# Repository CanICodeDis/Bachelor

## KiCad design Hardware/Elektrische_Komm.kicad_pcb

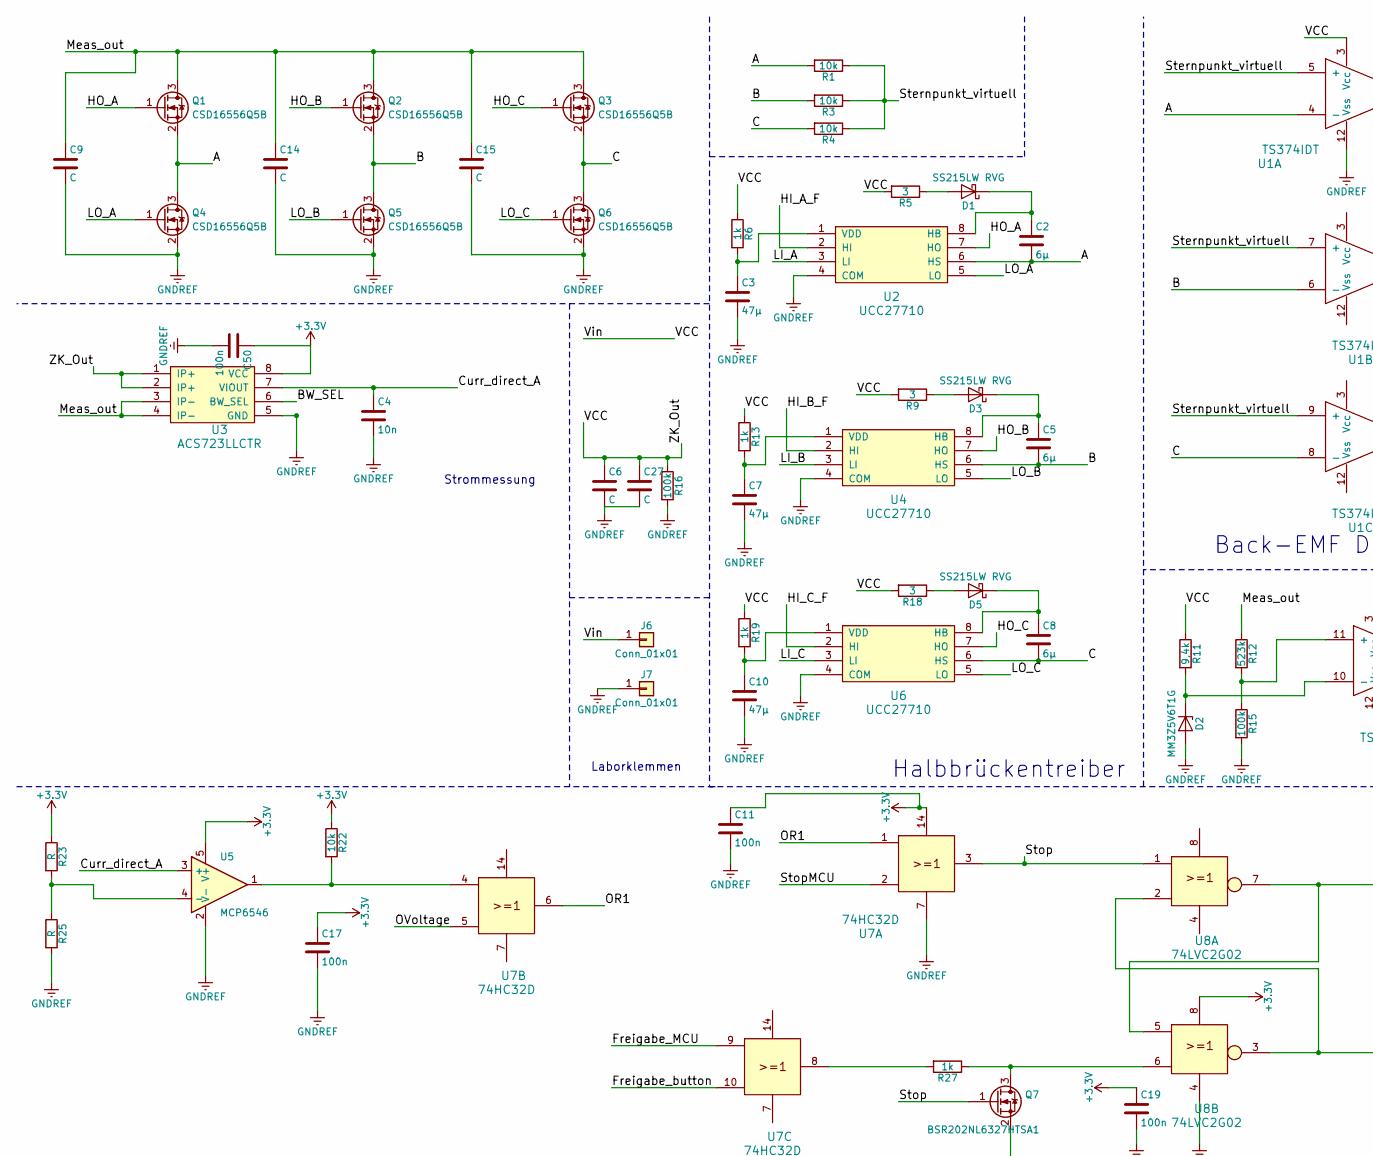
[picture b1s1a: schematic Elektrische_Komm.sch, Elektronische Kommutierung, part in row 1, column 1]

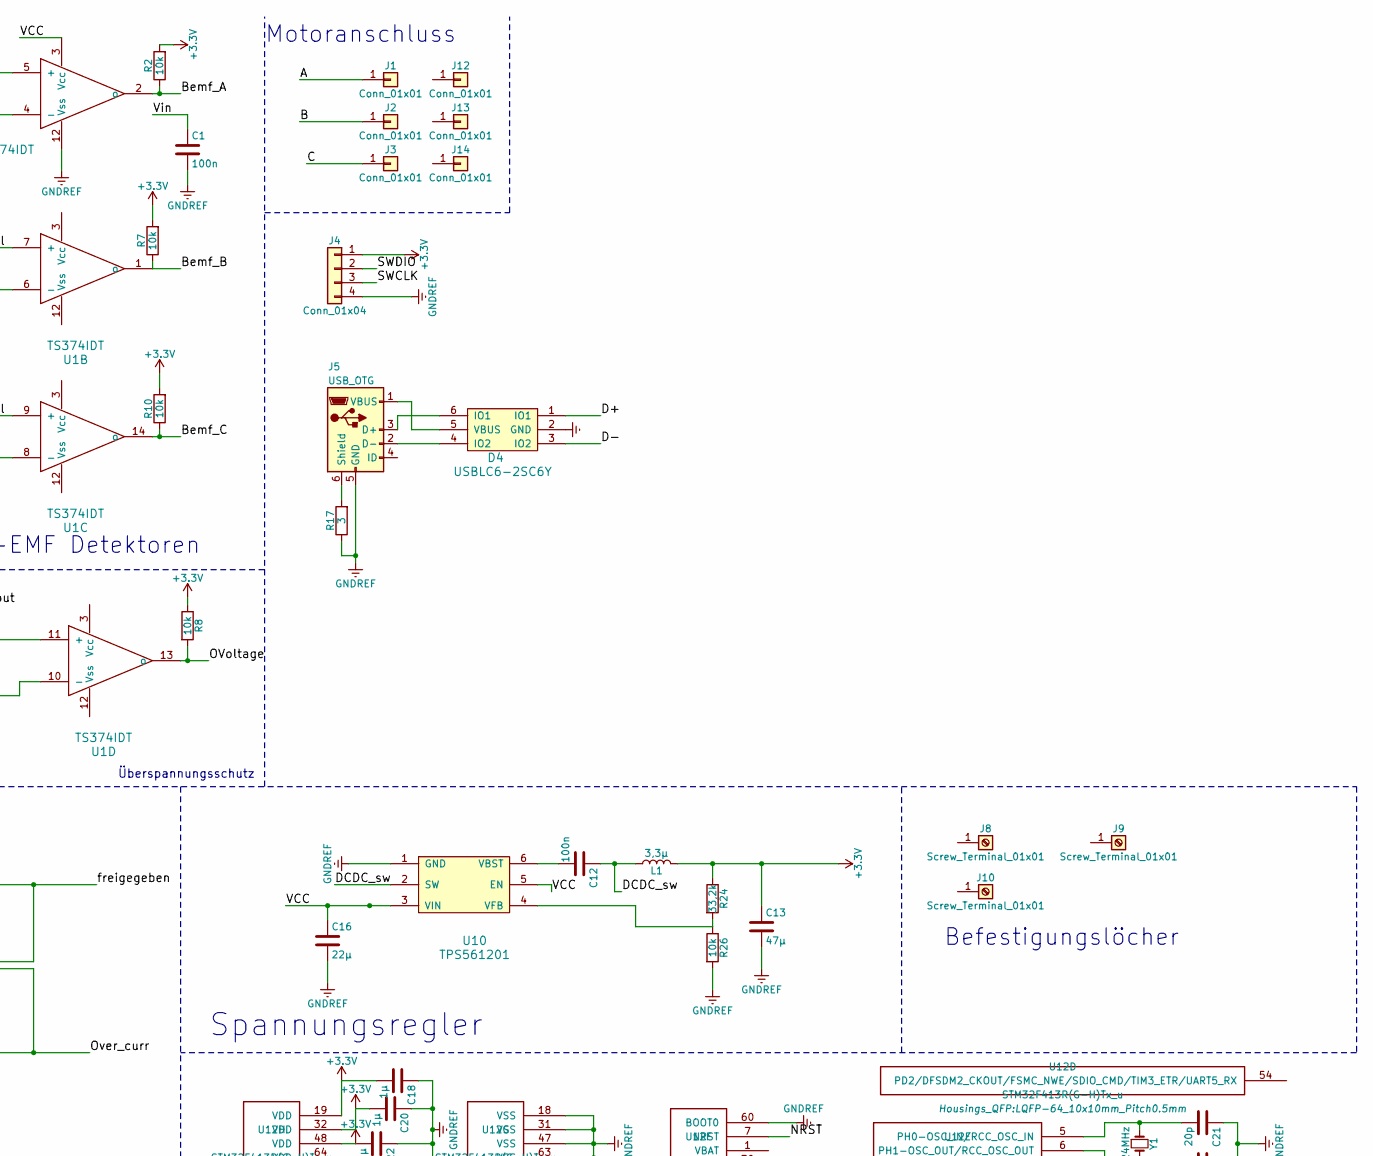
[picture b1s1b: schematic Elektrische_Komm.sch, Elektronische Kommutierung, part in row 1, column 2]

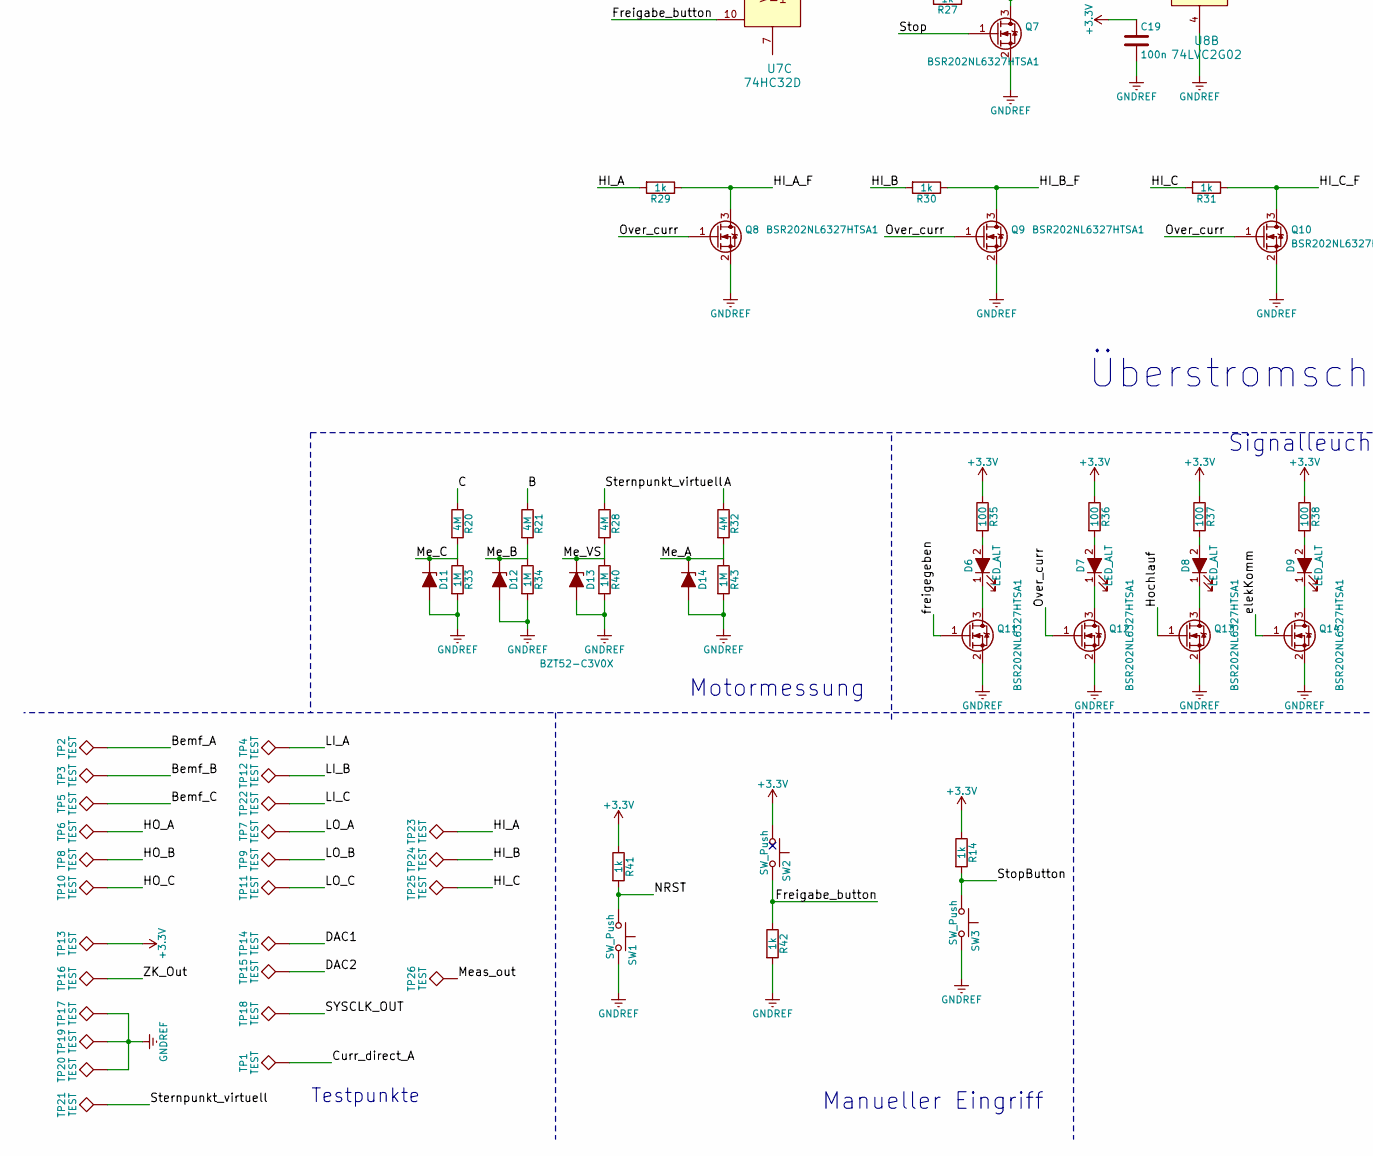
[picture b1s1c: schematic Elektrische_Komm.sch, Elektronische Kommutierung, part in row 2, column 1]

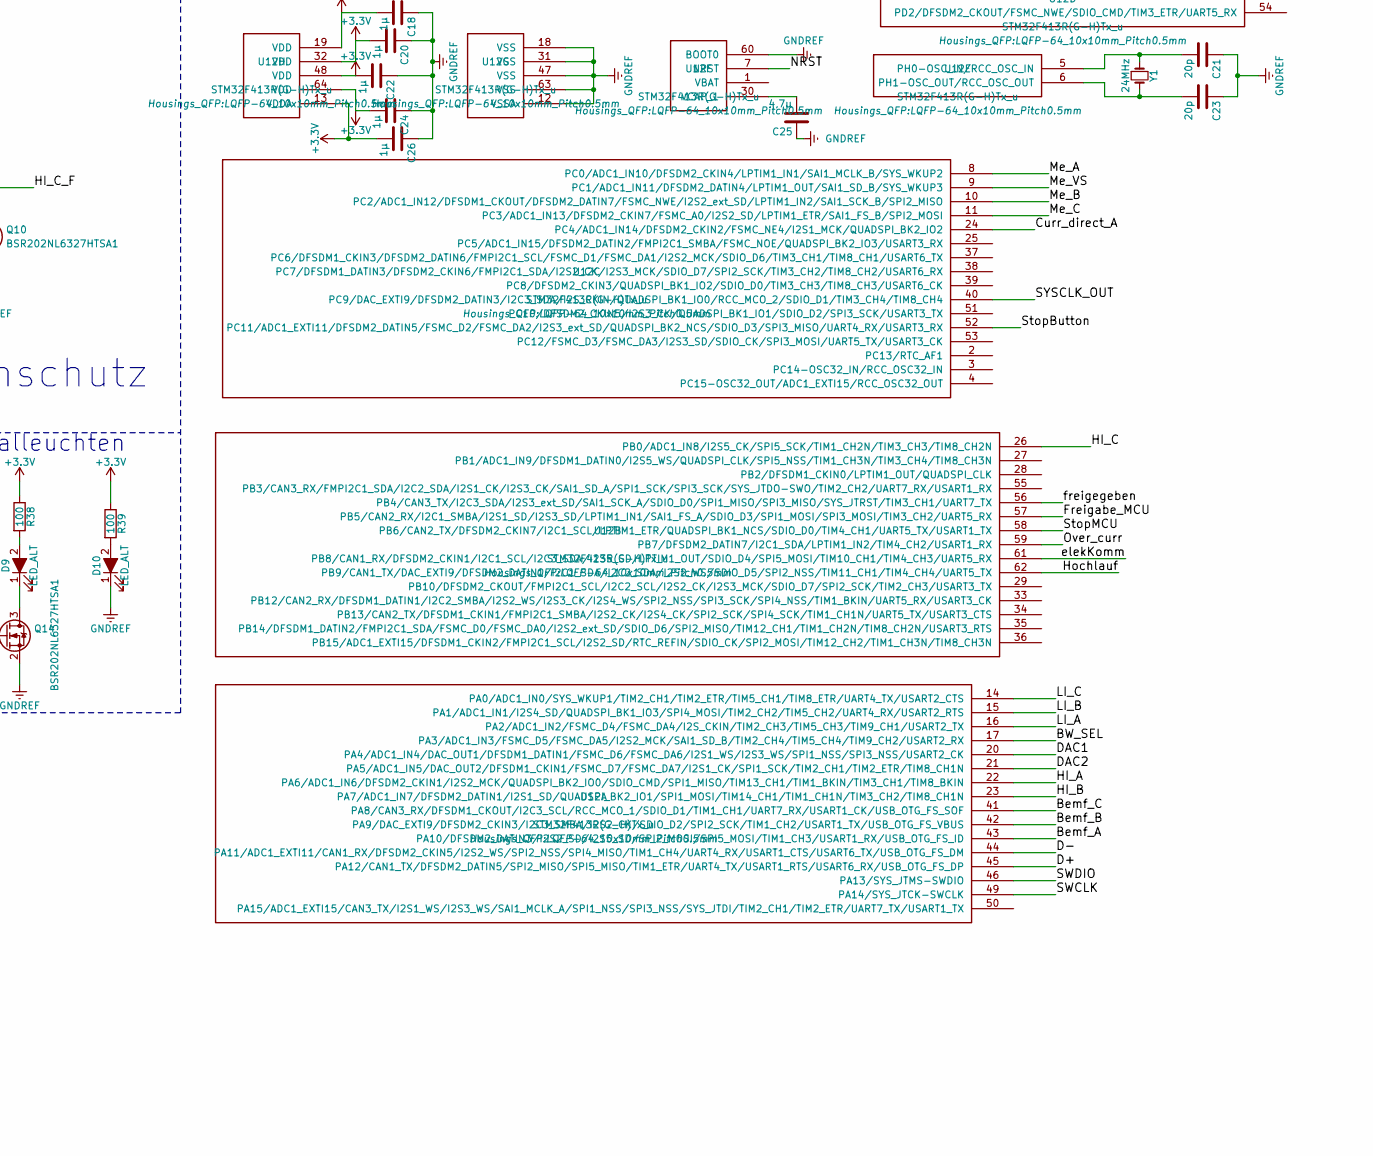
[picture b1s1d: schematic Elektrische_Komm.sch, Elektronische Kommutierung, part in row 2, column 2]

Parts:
C1, C11, C12, C17, C19, C50: 100n; C_0603
C2, C5, C8: 6µ; R_0603
C3, C7, C10, C13: 47µ; C_0805
C4: 10n; C_0603
C6, C27: C; CP_Radial_D10.0mm_P5.00mm
C9, C14, C15: C; C_1812
C16: 22µ; C_1210
C18, C20, C22, C24, C26: 1µ; C_0603
C21, C23: 20p; C_0603
C25: 4,7µ; C_0603
D1, D3, D5: SS215LW RVG; D_SOD-123F
D2: MM3Z5V6T1G; D_SOD-323
D4: USBLC6-2SC6Y; SOT-23-6
D6, D7: LED_ALT; LED_0805_HandSoldering
D8, D9, D10: LED_ALT; LED_0805
D11, D12, D13, D14: BZT52-C3V0X; D_SOD-123
J1, J2, J3: Conn_01x01; MotorConn
J4: Conn_01x04; JST_EH_B04B-EH-A_04x2.50mm_Straight
J5: USB_OTG; USB_Micro-B_Molex-105017-0001
J6, J7: Conn_01x01; Laborbuchse
J8, J9, J10: Screw_Terminal_01x01; MountingHole_3.2mm_M3_DIN965
J12, J13, J14: Conn_01x01; Führungsloch
L1: 3,3µ; SRN3015-3R3M
Q1, Q2, Q3, Q4, Q5, Q6: CSD16556Q5B; SON5x6
Q7, Q8, Q9, Q10, Q11, Q12, Q13, Q14: BSR202NL6327HTSA1; SC-59
R1, R2, R3, R4, R7, R8, R10, R22, R26: 10k; R_0603
R5, R9, R18: 3; R_1210
R6, R13, R14, R19, R27, R29, R30, R31, R41, R42: 1k; R_0603
R11: 9,4k; R_0603
R12: 523k; R_0603
R15, R16: 100k; R_0603
R17: 3; R_0603
R20, R21, R28, R32: 4M; R_0603
R23, R25: R; R_0603
R24: 33,2k; R_0603
R33, R34, R40, R43: 1M; R_0603
R35, R36, R37, R38, R39: 100; R_0603
SW1, SW2, SW3: SW_Push; Switch
TP1, TP2, TP3, TP4, TP5, TP6, TP7, TP8, TP9, TP10, TP11, TP12, TP13, TP14, TP15, TP16, TP17, TP18, TP19, TP20, TP21, TP22, TP23, TP24, TP25, TP26: TEST; Pin_Header_Straight_1x01_Pitch1.00mm
U1: TS374IDT; SOIC-14_3.9x8.7mm_Pitch1.27mm
U2, U4, U6: UCC27710; SOIC-8_3.9x4.9mm_Pitch1.27mm
U3: ACS723LLCTR; SOIC-8_3.9x4.9mm_Pitch1.27mm
U5: MCP6546; SOT-23-5
U7: 74HC32D; TSSOP-14_4.4x5mm_Pitch0.65mm
U8: 74LVC2G02; TSSOP-8_3x3mm_Pitch0.65mm
U10: TPS561201; SOT-23-6
U12: STM32F413R(G-H)Tx_u; LQFP-64_10x10mm_Pitch0.5mm
Y1: 24MHz; FQ5032A

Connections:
+3V3: C11.1, C13.1, C17.1, C18.2, C19.1, C20.2, C22.2, C24.2, C26.2, C50.1, J4.1, L1.2, R2.2, R7.2, R8.1, R10.2, R14.1, R22.1, R23.1, R24.1, R35.1, R36.1, R37.1, R38.1, R39.1, R41.1, SW2.1, TP13.1, U3.8 (VCC), U5.5 (V+), U7.14, U8.8, U12.13 (VDDA), U12.19 (VDD), U12.32 (VDD), U12.48 (VDD), U12.64 (VDD)
/A: C2.2, J1.1, Q1.2 (S), Q4.3 (D), R1.2, R32.1, U1.4 (-), U2.6 (HS)
/B: C5.2, J2.1, Q2.2 (S), Q5.3 (D), R3.2, R21.1, U1.6 (-), U4.6 (HS)
/BW_SEL: U3.6 (BW_SEL), U12.17 (PA3/ADC1_IN3/FSMC_D5/FSMC_DA5/I2S2_MCK/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)
/Bemf_A: R2.1, TP2.1, U1.2 (o), U12.43 (PA10/DFSDM2_DATIN3/I2S2_SD/I2S5_SD/SPI2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)
/Bemf_B: R7.1, TP3.1, U1.1 (o), U12.42 (PA9/DAC_EXTI9/DFSDM2_CKIN3/I2C3_SMBA/I2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)
/Bemf_C: R10.1, TP5.1, U1.14 (o), U12.41 (PA8/CAN3_RX/DFSDM1_CKOUT/I2C3_SCL/RCC_M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)
/C: C8.2, J3.1, Q3.2 (S), Q6.3 (D), R4.2, R20.1, U1.8 (-), U6.6 (HS)
/Curr_direct_A: C4.1, TP1.1, U3.7 (VIOUT), U5.3 (+), U12.24 (PC4/ADC1_IN14/DFSDM2_CKIN2/FSMC_NE4/I2S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)
/D+: D4.1 (IO1), U12.45 (PA12/CAN1_TX/DFSDM2_DATIN5/SPI2_MISO/SP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)
/D-: D4.3 (IO2), U12.44 (PA11/ADC1_EXTI11/CAN1_RX/DFSDM2_CKIN5/I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)
/DAC1: TP14.1, U12.20 (PA4/ADC1_IN4/DAC_OUT1/DFSDM1_DATIN1/FSM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)
/DAC2: TP15.1, U12.21 (PA5/ADC1_IN5/DAC_OUT2/DFSDM1_CKIN1/FSMC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)
/DCDC_sw: C12.1, L1.1, U10.2 (SW)
/Freigabe_MCU: U7.9, U12.57 (PB5/CAN2_RX/I2C1_SMBA/I2S1_SD/I2S3_SD/L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)
/Freigabe_button: R42.1, SW2.2, U7.10
/HI_A: R29.2, TP23.1, U12.22 (PA6/ADC1_IN6/DFSDM2_CKIN1/I2S2_MCK/QUAD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)
/HI_A_F: Q8.3 (D), R29.1, U2.2 (HI)
/HI_B: R30.2, TP24.1, U12.23 (PA7/ADC1_IN7/DFSDM2_DATIN1/I2S1_SD/QUAD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)
/HI_B_F: Q9.3 (D), R30.1, U4.2 (HI)
/HI_C: R31.2, TP25.1, U12.26 (PB0/ADC1_IN8/I2S5_CK/SPI5_SCK/TIM1_CH2N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)
/HI_C_F: Q10.3 (D), R31.1, U6.2 (HI)
/HO_A: Q1.1 (G), TP6.1, U2.7 (HO)
/HO_B: Q2.1 (G), TP8.1, U4.7 (HO)
/HO_C: Q3.1 (G), TP10.1, U6.7 (HO)
/Hochlauf: Q13.1 (G), U12.62 (PB9/CAN1_TX/DAC_EXTI9/DFSDM2_DATIN1/I2C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)
/LI_A: TP4.1, U2.3 (LI), U12.16 (PA2/ADC1_IN2/FSMC_D4/FSMC_DA4/I2S_CKIN/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)
/LI_B: TP12.1, U4.3 (LI), U12.15 (PA1/ADC1_IN1/I2S4_SD/QUADSPI_BK1_IO3/SP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)
/LI_C: TP22.1, U6.3 (LI), U12.14 (PA0/ADC1_IN0/SYS_WKUP1/TIM2_CH1/TIM2_ET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)
/LO_A: Q4.1 (G), TP7.1, U2.5 (LO)
/LO_B: Q5.1 (G), TP9.1, U4.5 (LO)
/LO_C: Q6.1 (G), TP11.1, U6.5 (LO)
/Me_A: D14.1 (K), R32.2, R43.1, U12.8 (PC0/ADC1_IN10/DFSDM2_CKIN4/LPTIM1_IN1/S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)
/Me_B: D12.1 (K), R21.2, R34.1, U12.10 (PC2/ADC1_IN12/DFSDM1_CKOUT/DFSDM2_DATIN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)
/Me_C: D11.1 (K), R20.2, R33.1, U12.11 (PC3/ADC1_IN13/DFSDM2_CKIN7/FSMC_A0/I2S2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)
/Me_VS: D13.1 (K), R28.2, R40.1, U12.9 (PC1/ADC1_IN11/DFSDM2_DATIN4/LPTIM1_OUT/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)
/Meas_out: C9.1, C14.1, C15.1, Q1.3 (D), Q2.3 (D), Q3.3 (D), R12.1, TP26.1, U3.3 (IP-), U3.4 (IP-)
/NRST: R41.2, SW1.1, U12.7 (NRST)
/OR1: U7.1, U7.6
/OVoltage: R8.2, U1.13 (o), U7.5
/Over_curr: Q8.1 (G), Q9.1 (G), Q10.1 (G), Q12.1 (G), U8.2, U8.3, U12.59 (PB7/DFSDM2_DATIN7/I2C1_SDA/LPTIM1_IN2/T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)
/SWCLK: J4.3, U12.49 (PA14/SYS_JTCK-SWCLK)
/SWDIO: J4.2, U12.46 (PA13/SYS_JTMS-SWDIO)
/SYSCLK_OUT: TP18.1, U12.40 (PC9/DAC_EXTI9/DFSDM2_DATIN3/I2C3_SDA/I2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)
/Sternpunkt_virtuell: R1.1, R3.1, R4.1, R28.1, TP21.1, U1.5 (+), U1.7 (+), U1.9 (+)
/Stop: Q7.1 (G), U7.3, U8.1
/StopButton: R14.2, SW3.1, U12.52 (PC11/ADC1_EXTI11/DFSDM2_DATIN5/FSMC_D2/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)
/StopMCU: U7.2, U12.58 (PB6/CAN2_TX/DFSDM2_CKIN7/I2C1_SCL/LPTIM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)
/VCC: C1.1, C6.1, C16.1, C27.1, J6.1, R5.2, R6.1, R9.2, R11.1, R13.1, R16.1, R18.2, R19.1, TP16.1, U1.3 (Vcc), U3.1 (IP+), U3.2 (IP+), U10.3 (VIN), U10.5 (EN)
/elekKomm: Q14.1 (G), U12.61 (PB8/CAN1_RX/DFSDM2_CKIN1/I2C1_SCL/I2C3_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)
/freigegeben: Q11.1 (G), U8.5, U8.7, U12.56 (PB4/CAN3_TX/I2C3_SDA/I2S3_ext_SD/SAI1_S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)
GNDREF: C1.2, C3.2, C4.2, C6.2, C7.2, C9.2, C10.2, C11.2, C13.2, C14.2, C15.2, C16.2, C17.2, C18.1, C19.2, C20.1, C21.1, C22.1, C23.1, C24.1, C25.1, C26.1, C27.2, C50.2, D2.2 (A), D4.2 (GND), D10.1 (K), D11.2 (A), D12.2 (A), D13.2 (A), D14.2 (A), J4.4, J5.5 (GND), J7.1, Q4.2 (S), Q5.2 (S), Q6.2 (S), Q7.2 (S), Q8.2 (S), Q9.2 (S), Q10.2 (S), Q11.2 (S), Q12.2 (S), Q13.2 (S), Q14.2 (S), R15.2, R16.2, R17.1, R25.2, R26.2, R33.2, R34.2, R40.2, R42.2, R43.2, SW1.2, SW3.2, TP17.1, TP19.1, TP20.1, U1.12 (Vss), U2.4 (COM), U3.5 (GND), U4.4 (COM), U5.2 (V-), U6.4 (COM), U7.7, U8.4, U10.1 (GND), U12.12 (VSSA), U12.18 (VSS), U12.31 (VSS), U12.47 (VSS), U12.60 (BOOT0), U12.63 (VSS)
unnamed: C2.1, D1.1 (K), U2.8 (HB)
unnamed: C3.1, R6.2, U2.1 (VDD)
unnamed: C5.1, D3.1 (K), U4.8 (HB)
unnamed: C7.1, R13.2, U4.1 (VDD)
unnamed: C8.1, D5.1 (K), U6.8 (HB)
unnamed: C10.1, R19.2, U6.1 (VDD)
unnamed: C12.2, U10.6 (VBST)
unnamed: C21.2, U12.5 (PH0-OSC_IN/RCC_OSC_IN), Y1.1
unnamed: C23.2, U12.6 (PH1-OSC_OUT/RCC_OSC_OUT), Y1.2
unnamed: C25.2, U12.30 (VCAP_1)
unnamed: D1.2 (A), R5.1
unnamed: D2.1 (K), R11.2, U1.10 (-)
unnamed: D3.2 (A), R9.1
unnamed: D4.4 (IO2), J5.2 (D-)
unnamed: D4.5 (VBUS), J5.1 (VBUS)
unnamed: D4.6 (IO1), J5.3 (D+)
unnamed: D5.2 (A), R18.1
unnamed: D6.1 (K), Q11.3 (D)
unnamed: D6.2 (A), R35.2
unnamed: D7.1 (K), Q12.3 (D)
unnamed: D7.2 (A), R36.2
unnamed: D8.1 (K), Q13.3 (D)
unnamed: D8.2 (A), R37.2
unnamed: D9.1 (K), Q14.3 (D)
unnamed: D9.2 (A), R38.2
unnamed: D10.2 (A), R39.2
unnamed: J5.6 (Shield), R17.2
unnamed: Q7.3 (D), R27.1, U8.6
unnamed: R12.2, R15.1, U1.11 (+)
unnamed: R22.2, U5.1, U7.4
unnamed: R23.2, R25.1, U5.4 (-)
unnamed: R24.2, R26.1, U10.4 (VFB)
unnamed: R27.2, U7.8

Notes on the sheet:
Halbbrückentreiber
Überstromschutz
Signalleuchten
Spannungsregler
Motoranschluss
Testpunkte
Back-EMF Detektoren
Strommessung
Befestigungslöcher
Überspannungsschutz
Laborklemmen
Manueller Eingriff
Motormessung

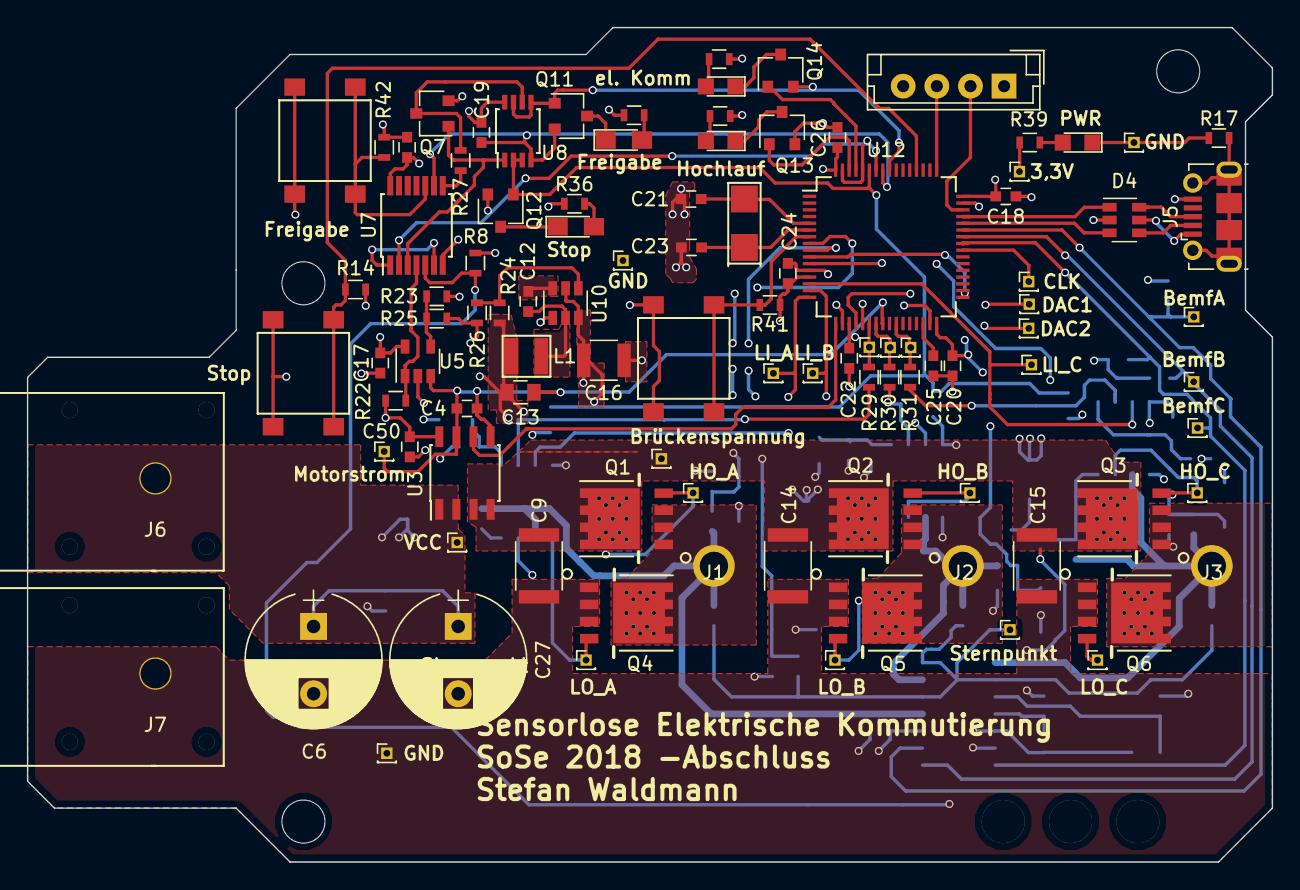
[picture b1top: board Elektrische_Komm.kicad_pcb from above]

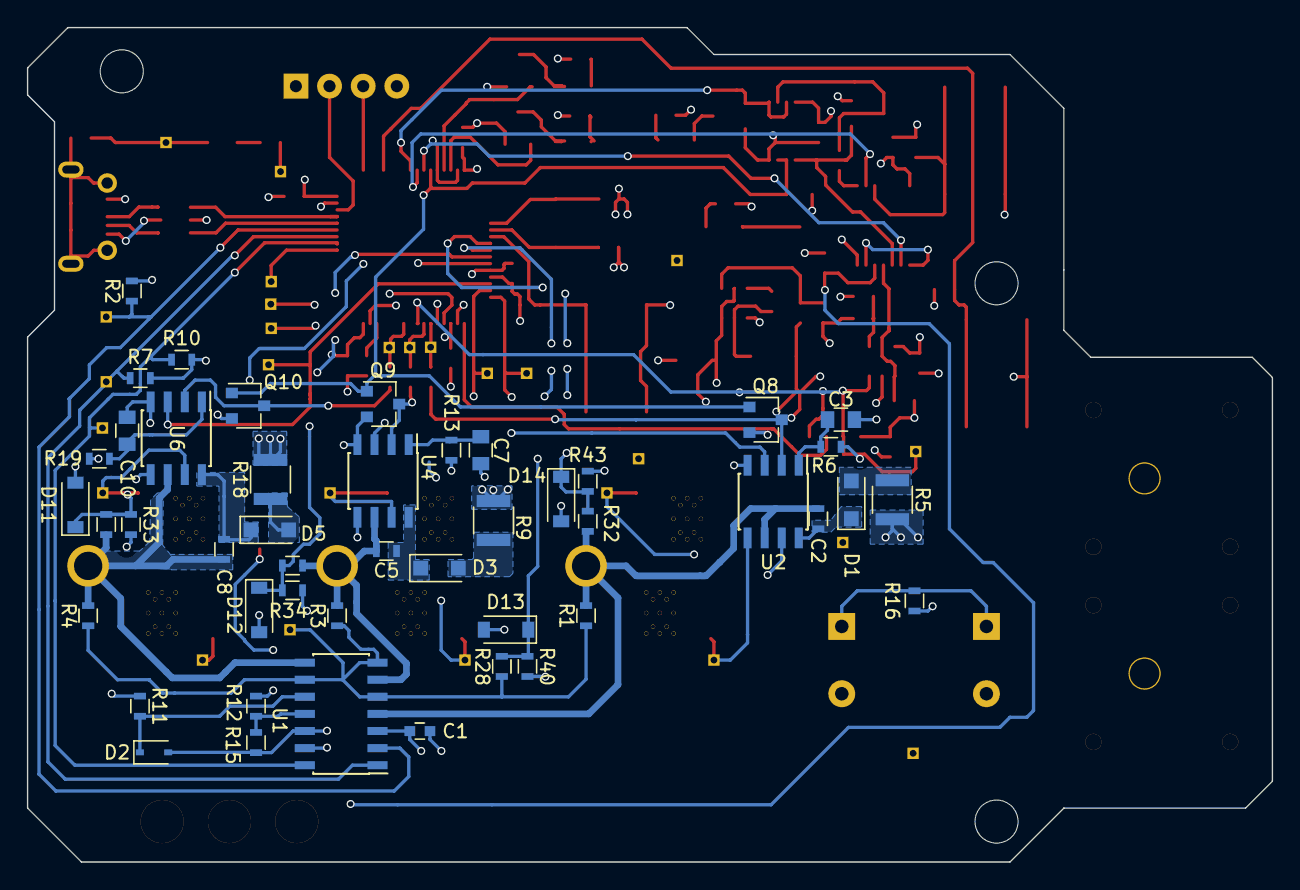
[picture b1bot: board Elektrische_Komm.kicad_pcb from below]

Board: 4 copper layers, 92.5 x 62.0 mm, 153 parts (46 on the bottom side), 85 nets.

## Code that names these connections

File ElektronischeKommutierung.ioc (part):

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Mcu.Name=STM32F413R(G-H)Tx
Mcu.Package=LQFP64
Mcu.UserName=STM32F413RGTx
PA0.GPIOParameters=GPIO_Speed,GPIO_Label
PA0.GPIO_Label=LI_A
PA0.GPIO_Speed=GPIO_SPEED_FREQ_VERY_HIGH
PA0.Signal=GPIO_Output
PA1.GPIOParameters=GPIO_Speed,GPIO_Label
PA1.GPIO_Label=LI_B
PA1.GPIO_Speed=GPIO_SPEED_FREQ_VERY_HIGH
PA1.Signal=GPIO_Output
PA10.GPIOParameters=GPIO_Speed,GPIO_Label
PA10.GPIO_Label=BEMF_A
PA10.GPIO_Speed=GPIO_SPEED_FREQ_VERY_HIGH
PA10.Signal=S_TIM1_CH3
PA11.Mode=Device_Only
PA11.Signal=USB_OTG_FS_DM
PA12.Mode=Device_Only
PA12.Signal=USB_OTG_FS_DP
PA13.Mode=Serial_Wire
PA13.Signal=SYS_JTMS-SWDIO
PA14.Mode=Serial_Wire
PA14.Signal=SYS_JTCK-SWCLK
PA2.GPIOParameters=GPIO_Speed,GPIO_Label
PA2.GPIO_Label=LI_C
PA2.GPIO_Speed=GPIO_SPEED_FREQ_VERY_HIGH
PA2.Signal=GPIO_Output
PA3.GPIOParameters=GPIO_Speed,GPIO_Label
PA3.GPIO_Label=BW_SEL
PA3.GPIO_Speed=GPIO_SPEED_FREQ_MEDIUM
PA3.Signal=GPIO_Output
PA4.Signal=COMP_DAC1_group
PA5.Signal=COMP_DAC2_group
PA6.GPIOParameters=GPIO_Speed
PA6.GPIO_Speed=GPIO_SPEED_FREQ_VERY_HIGH
PA6.Signal=S_TIM3_CH1
PA7.GPIOParameters=GPIO_Speed
PA7.GPIO_Speed=GPIO_SPEED_FREQ_VERY_HIGH
PA7.Signal=S_TIM3_CH2
PA8.GPIOParameters=GPIO_Speed,GPIO_Label
PA8.GPIO_Label=BEMF_C
PA8.GPIO_Speed=GPIO_SPEED_FREQ_VERY_HIGH
PA8.Signal=S_TIM1_CH1
PA9.GPIOParameters=GPIO_Speed,GPIO_Label
PA9.GPIO_Label=BEMF_B
PA9.GPIO_Speed=GPIO_SPEED_FREQ_VERY_HIGH
PA9.Signal=S_TIM1_CH2
PB0.GPIOParameters=GPIO_Speed
PB0.GPIO_Speed=GPIO_SPEED_FREQ_VERY_HIGH
PB0.Signal=S_TIM3_CH3
PB4.GPIOParameters=GPIO_Label
PB4.GPIO_Label=freigegeben
PB4.Signal=GPXTI4
PB5.GPIOParameters=GPIO_Speed,GPIO_Label
PB5.GPIO_Label=FreigabeMCU
PB5.GPIO_Speed=GPIO_SPEED_FREQ_MEDIUM
PB5.Signal=GPIO_Output
PB6.GPIOParameters=GPIO_Speed,GPIO_Label
PB6.GPIO_Label=StopMCU
PB6.GPIO_Speed=GPIO_SPEED_FREQ_VERY_HIGH
PB6.Signal=GPIO_Output
PB7.GPIOParameters=GPIO_Label
PB7.GPIO_Label=OverCurr
PB7.Signal=GPXTI7
PB8.GPIOParameters=GPIO_Speed,GPIO_Label
PB8.GPIO_Label=elekKomm
PB8.GPIO_Speed=GPIO_SPEED_FREQ_LOW
PB8.Signal=GPIO_Output
PB9.GPIOParameters=GPIO_Label
PB9.GPIO_Label=Hochlauf
PB9.Signal=GPIO_Output
PC0.GPIOParameters=GPIO_Label
PC0.GPIO_Label=Me_A
PC0.Signal=ADCx_IN10
PC1.GPIOParameters=GPIO_Label
PC1.GPIO_Label=Me_VS
PC1.Signal=ADCx_IN11
PC11.GPIOParameters=GPIO_Label
PC11.GPIO_Label=StopButton
PC11.Signal=GPXTI11
PC2.GPIOParameters=GPIO_Label
PC2.GPIO_Label=Me_B
PC2.Signal=ADCx_IN12
PC3.GPIOParameters=GPIO_Label
PC3.GPIO_Label=Me_C
PC3.Signal=ADCx_IN13
PC4.GPIOParameters=GPIO_Label
PC4.GPIO_Label=CurrDirectA
PC4.Signal=ADCx_IN14
PC9.GPIOParameters=GPIO_Speed,GPIO_Label
PC9.GPIO_Label=ClockOut
PC9.GPIO_Speed=GPIO_SPEED_FREQ_VERY_HIGH
PC9.Mode=Clock-out-2
PC9.Signal=RCC_MCO_2
PH0\ -\ OSC_IN.Mode=HSE-External-Oscillator
PH0\ -\ OSC_IN.Signal=RCC_OSC_IN
PH1\ -\ OSC_OUT.Mode=HSE-External-Oscillator
PH1\ -\ OSC_OUT.Signal=RCC_OSC_OUT
RCC.HSE_VALUE=24000000
RCC.SYSCLKFreq_VALUE=96000000
RCC.SYSCLKSource=RCC_SYSCLKSOURCE_PLLCLK
board=ElektronischeKommutierung

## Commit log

2017-11-11 Startpunkt
2017-11-11 Literatur hinzugefügt
2018-05-14 Spannungsregler implementiert
2018-05-14 same
2018-05-16 ACS723-Datenblatt
2018-05-17 Netlist
2018-05-18 Schematic fertig
2018-05-24 Layout
2018-05-24 Korrektur Strommessung
2018-05-26 Zwei Strommesser
2018-05-27 _______________ < Neue Bauteile > --------------- \ / \ //\ \ |\___/| / \// \\ /0 0 \__ / // | \ \ / / \/_/ // | \ \ @_^_@'/ \/_ // | \ \ //_^_/ \/_ // | \ \ ( //) | \/// | \ \ ( / /) _|_ / ) // | \ 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
2018-05-28 _______________________ < Layout weitergeführt > ----------------------- \ / \ //\ \ |\___/| / \// \\ /0 0 \__ / // | \ \ / / \/_/ // | \ \ @_^_@'/ \/_ // | \ \ //_^_/ \/_ // | \ \ ( //) | \/// | \ \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
2018-06-01 _______________________________ < K_ind Berechnung hinzugefügt > ------------------------------- \ / \ //\ \ |\___/| / \// \\ /0 0 \__ / // | \ \ / / \/_/ // | \ \ @_^_@'/ \/_ // | \ \ //_^_/ \/_ // 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
2018-06-02 ______________________ < Layout weitergemacht > ---------------------- \ / \ //\ \ |\___/| / \// \\ /0 0 \__ / // | \ \ / / \/_/ // | \ \ @_^_@'/ \/_ // | \ \ //_^_/ \/_ // | \ \ ( //) | \/// | \ \ (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
2018-06-03 ___________________ < MOSFETS geändert > ------------------- \ / \ //\ \ |\___/| / \// \\ /0 0 \__ / // | \ \ / / \/_/ // | \ \ @_^_@'/ \/_ // | \ \ //_^_/ \/_ // | \ \ ( //) | \/// | \ \ ( / /) _|_ 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
2018-06-04 _____________________ < BW_SEL hinzugefügt > --------------------- \ / \ //\ \ |\___/| / \// \\ /0 0 \__ / // | \ \ / / \/_/ // | \ \ @_^_@'/ \/_ // | \ \ //_^_/ \/_ // | \ \ ( //) | \/// | \ \ ( / /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
2018-06-05 _________________ < Planes erledigt > ----------------- \ / \ //\ \ |\___/| / \// \\ /0 0 \__ / // | \ \ / / \/_/ // | \ \ @_^_@'/ \/_ // | \ \ //_^_/ \/_ // | \ \ ( //) | \/// | \ \ ( / /) _|_ / ) /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
2018-06-06 _____________________ < Layout Groundplanes > --------------------- \ / \ //\ \ |\___/| / \// \\ /0 0 \__ / // | \ \ / / \/_/ // | \ \ @_^_@'/ \/_ // | \ \ //_^_/ \/_ // | \ \ ( //) | \/// | \ \ ( / 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
2018-06-06 ________________ < Matlab-Skripte > ---------------- \ / \ //\ \ |\___/| / \// \\ /0 0 \__ / // | \ \ / / \/_/ // | \ \ @_^_@'/ \/_ // | \ \ //_^_/ \/_ // | \ \ ( //) | \/// | \ \ ( / /) _|_ / ) // |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
2018-06-15 ___________ < remodeled > ----------- \ / \ //\ \ |\___/| / \// \\ /0 0 \__ / // | \ \ / / \/_/ // | \ \ @_^_@'/ \/_ // | \ \ //_^_/ \/_ // | \ \ ( //) | \/// | \ \ ( / /) _|_ / ) // | \ _\ ( // /) '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
2018-06-15 ______________________ < Layout überarbeitet > ---------------------- \ / \ //\ \ |\___/| / \// \\ /0 0 \__ / // | \ \ / / \/_/ // | \ \ @_^_@'/ \/_ // | \ \ //_^_/ \/_ // | \ \ ( //) | \/// | \ \ ( 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
2018-06-18 ________________ < Mounting Holes > ---------------- \ / \ //\ \ |\___/| / \// \\ /0 0 \__ / // | \ \ / / \/_/ // | \ \ @_^_@'/ \/_ // | \ \ //_^_/ \/_ // | \ \ ( //) | \/// | \ \ ( / /) _|_ / ) // |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
2018-06-21 Board fertig
2018-06-25 _________________________ < Zener-Spannungsreferenz > ------------------------- \ / \ //\ \ |\___/| / \// \\ /0 0 \__ / // | \ \ / / \/_/ // | \ \ @_^_@'/ \/_ // | \ \ //_^_/ \/_ // | \ \ ( //) | \//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
2018-06-25 __________________ < Bestellformulare > ------------------ \ / \ //\ \ |\___/| / \// \\ /0 0 \__ / // | \ \ / / \/_/ // | \ \ @_^_@'/ \/_ // | \ \ //_^_/ \/_ // | \ \ ( //) | \/// | \ \ ( / /) _|_ / 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
2018-07-02 ________________________ < Gerber-Files geplottet > ------------------------ \ / \ //\ \ |\___/| / \// \\ /0 0 \__ / // | \ \ / / \/_/ // | \ \ @_^_@'/ \/_ // | \ \ //_^_/ \/_ // | \ \ ( //) | \/// |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
2018-07-03 __________________________ < Messstation hinzugefügt > -------------------------- \ / \ //\ \ |\___/| / \// \\ /0 0 \__ / // | \ \ / / \/_/ // | \ \ @_^_@'/ \/_ // | \ \ //_^_/ \/_ // | \ \ ( //) | \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
2018-07-03 _____________ < Gerberfiles > ------------- \ / \ //\ \ |\___/| / \// \\ /0 0 \__ / // | \ \ / / \/_/ // | \ \ @_^_@'/ \/_ // | \ \ //_^_/ \/_ // | \ \ ( //) | \/// | \ \ ( / /) _|_ / ) // | \ _\ ( /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
2018-07-03 _________ < ZipFule > --------- \ / \ //\ \ |\___/| / \// \\ /0 0 \__ / // | \ \ / / \/_/ // | \ \ @_^_@'/ \/_ // | \ \ //_^_/ \/_ // | \ \ ( //) | \/// | \ \ ( / /) _|_ / ) // | \ _\ ( // /) '/,_ _ 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
2018-07-03 ____________ < Gerber.zip > ------------ \ / \ //\ \ |\___/| / \// \\ /0 0 \__ / // | \ \ / / \/_/ // | \ \ @_^_@'/ \/_ // | \ \ //_^_/ \/_ // | \ \ ( //) | \/// | \ \ ( / /) _|_ / ) // | \ _\ ( // /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
2018-07-03 _______ < jetzt > ------- \ / \ //\ \ |\___/| / \// \\ /0 0 \__ / // | \ \ / / \/_/ // | \ \ @_^_@'/ \/_ // | \ \ //_^_/ \/_ // | \ \ ( //) | \/// | \ \ ( / /) _|_ / ) // | \ _\ ( // /) '/,_ _ _/ ( ;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
2018-07-03 ___________ < gewandelt > ----------- \ / \ //\ \ |\___/| / \// \\ /0 0 \__ / // | \ \ / / \/_/ // | \ \ @_^_@'/ \/_ // | \ \ //_^_/ \/_ // | \ \ ( //) | \/// | \ \ ( / /) _|_ / ) // | \ _\ ( // /) '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
2018-08-20 header files
